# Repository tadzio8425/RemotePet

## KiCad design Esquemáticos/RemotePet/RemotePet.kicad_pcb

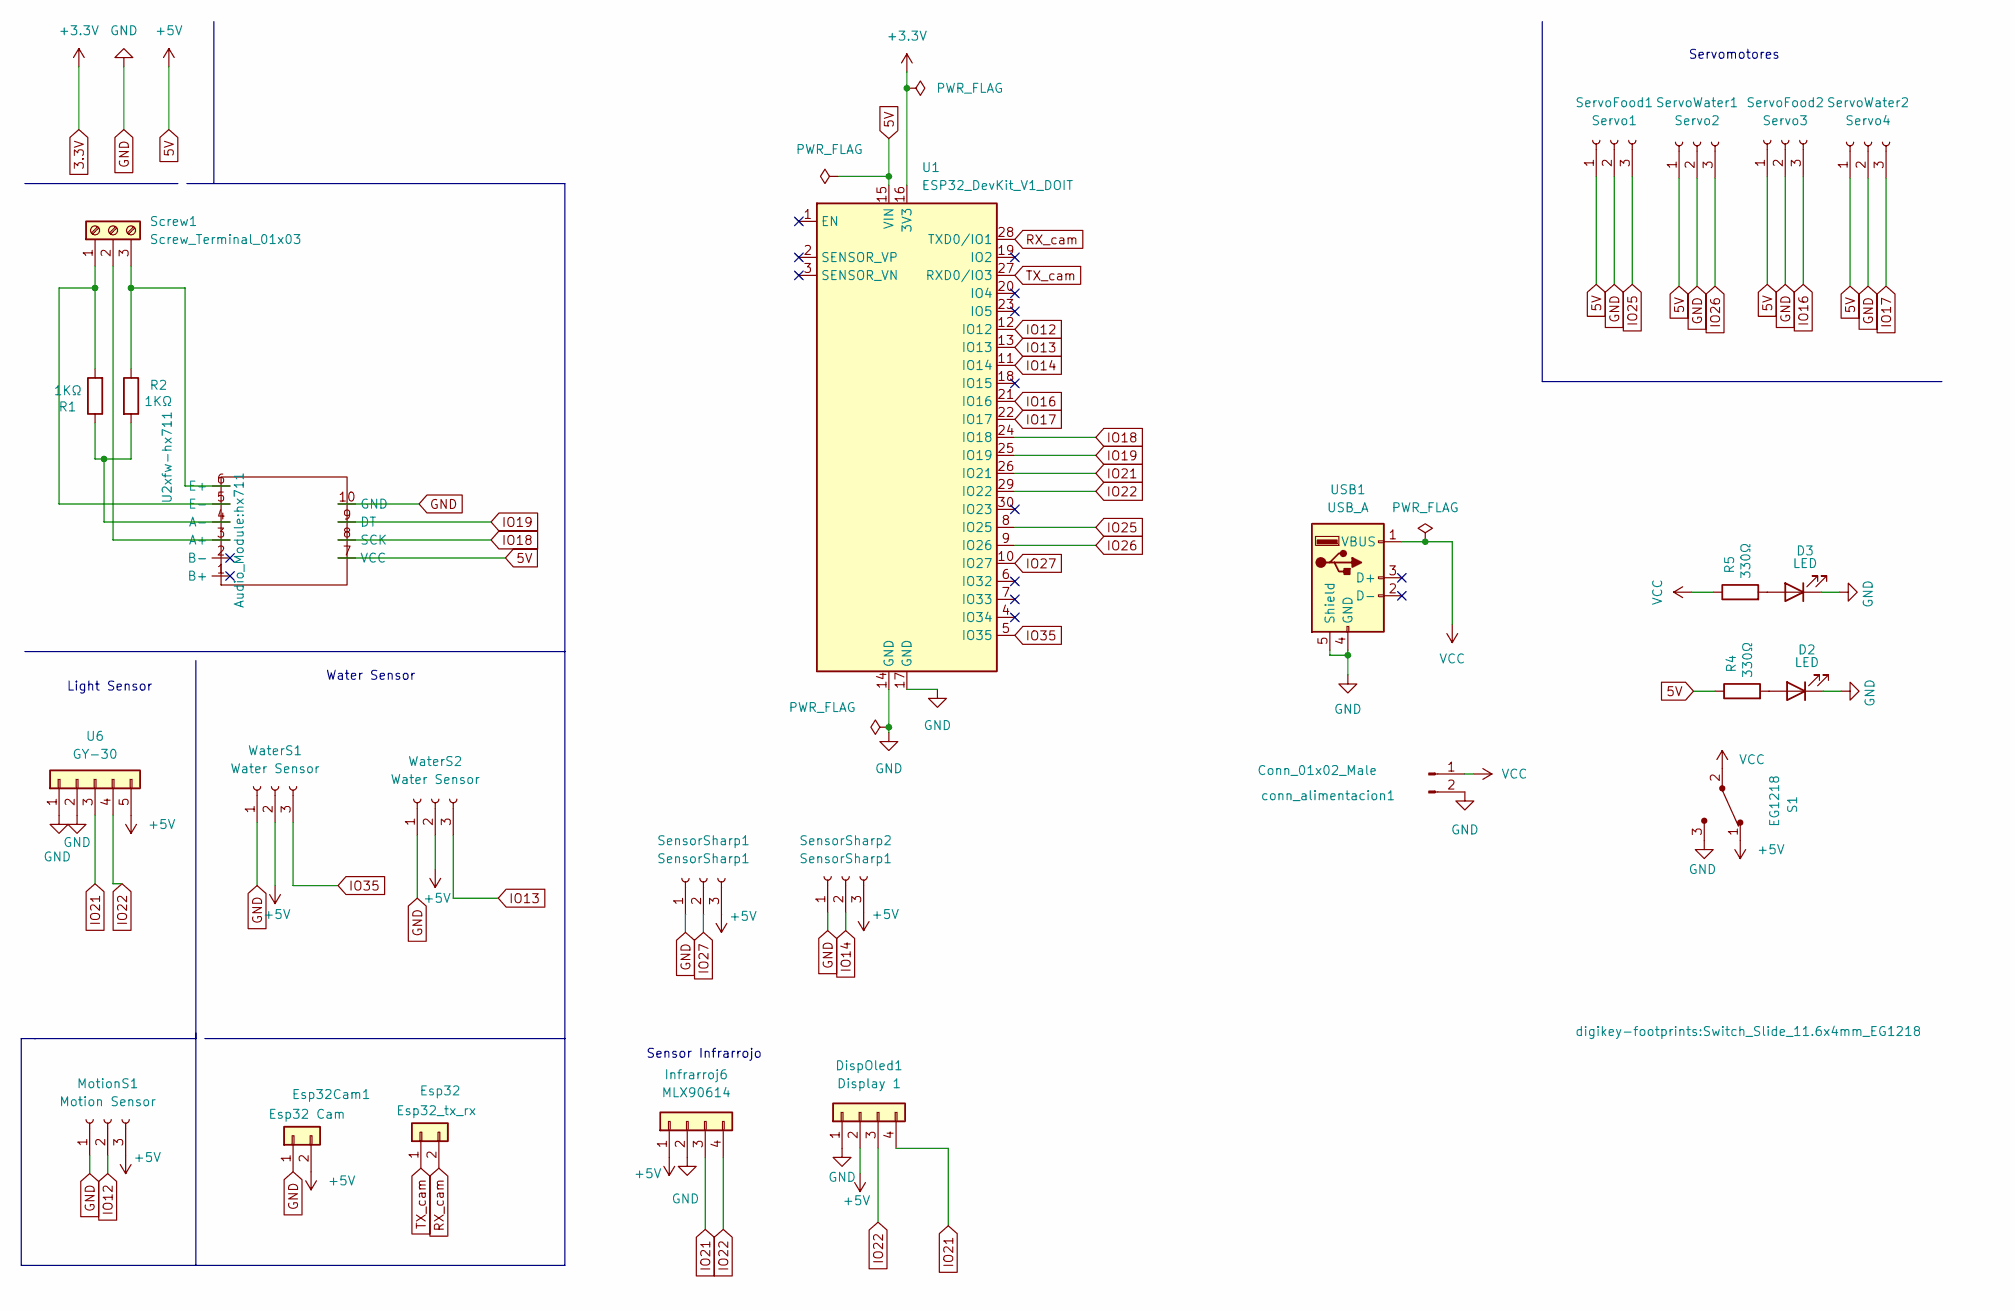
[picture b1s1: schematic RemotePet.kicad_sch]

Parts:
D2, D3: LED; LED_1210_3225Metric
DispOled1: Display 1; PinSocket_1x04_P2.54mm_Vertical
Esp32: Esp32_tx_rx; PinSocket_1x02_P2.54mm_Vertical
Esp32Cam1: Esp32 Cam; PinSocket_1x02_P2.54mm_Vertical
Infrarroj6: MLX90614; PinSocket_1x04_P2.54mm_Vertical
MotionS1: Motion Sensor; PinSocket_1x03_P2.54mm_Vertical
R1, R2: 1KΩ; R_0805_2012Metric
R4, R5: 330Ω; R_0805_2012Metric
S1: EG1218; Switch_Slide_11.6x4mm_EG1218; MPN EG1218; Digi-Key_PN EG1903-ND
Screw1: Screw_Terminal_01x03; TerminalBlock_bornier-3_P5.08mm
SensorSharp1, SensorSharp2: SensorSharp1; PinSocket_1x03_P2.54mm_Vertical
ServoFood1: Servo1; PinSocket_1x03_P2.54mm_Vertical
ServoFood2: Servo3; PinSocket_1x03_P2.54mm_Vertical
ServoWater1: Servo2; PinSocket_1x03_P2.54mm_Vertical
ServoWater2: Servo4; PinSocket_1x03_P2.54mm_Vertical
U1: ESP32_DevKit_V1_DOIT; esp32_devkit_v1_doit
U2: xfw-hx711; hx711
U6: GY-30; PinSocket_1x05_P2.54mm_Vertical
USB1: USB_A; USB_A_CONNFLY_DS1095-WNR0
WaterS1, WaterS2: Water Sensor; PinSocket_1x03_P2.54mm_Vertical
conn_alimentacion1: Conn_01x02_Male; PinSocket_1x02_P2.54mm_Vertical

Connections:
3.3V: U1.16 (3V3)
5V: DispOled1.2, Esp32Cam1.2, Infrarroj6.1, MotionS1.3, R4.1, S1.1, SensorSharp1.3, SensorSharp2.3, ServoFood1.1, ServoFood2.1, ServoWater1.1, ServoWater2.1, U1.15 (VIN), U2.7 (VCC), U6.5, WaterS1.2, WaterS2.2
GND: D2.1 (K), D3.1 (K), DispOled1.1, Esp32Cam1.1, Infrarroj6.2, MotionS1.1, S1.3, SensorSharp1.1, SensorSharp2.1, ServoFood1.2, ServoFood2.2, ServoWater1.2, ServoWater2.2, U1.14 (GND), U1.17 (GND), U2.10 (GND), U6.1, U6.2, USB1.4 (GND), USB1.5 (Shield), WaterS1.1, WaterS2.1, conn_alimentacion1.2
IO12: MotionS1.2, U1.12 (IO12)
IO13: U1.13 (IO13), WaterS2.3
IO14: SensorSharp2.2, U1.11 (IO14)
IO16: ServoFood2.3, U1.21 (IO16)
IO17: ServoWater2.3, U1.22 (IO17)
IO18: U1.24 (IO18), U2.8 (SCK)
IO19: U1.25 (IO19), U2.9 (DT)
IO21: DispOled1.4, Infrarroj6.3, U1.26 (IO21), U6.3
IO22: DispOled1.3, Infrarroj6.4, U1.29 (IO22), U6.4
IO25: ServoFood1.3, U1.8 (IO25)
IO26: ServoWater1.3, U1.9 (IO26)
IO27: SensorSharp1.2, U1.10 (IO27)
IO35: U1.5 (IO35), WaterS1.3
unnamed: D2.2 (A), R4.2
unnamed: R1.1, R2.2, U2.4 (A-)
unnamed: R1.2, Screw1.1, U2.5 (E-)
unnamed: R2.1, Screw1.3, U2.6 (E+)
unnamed: D3.2 (A), R5.2
unnamed: Screw1.2, U2.3 (A+)
RX_cam: Esp32.2, U1.28 (TXD0/IO1)
TX_cam: Esp32.1, U1.27 (RXD0/IO3)
VCC: R5.1, S1.2, USB1.1 (VBUS), conn_alimentacion1.1

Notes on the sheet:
Sensor Infrarrojo
Water Sensor
Light Sensor
Servomotores

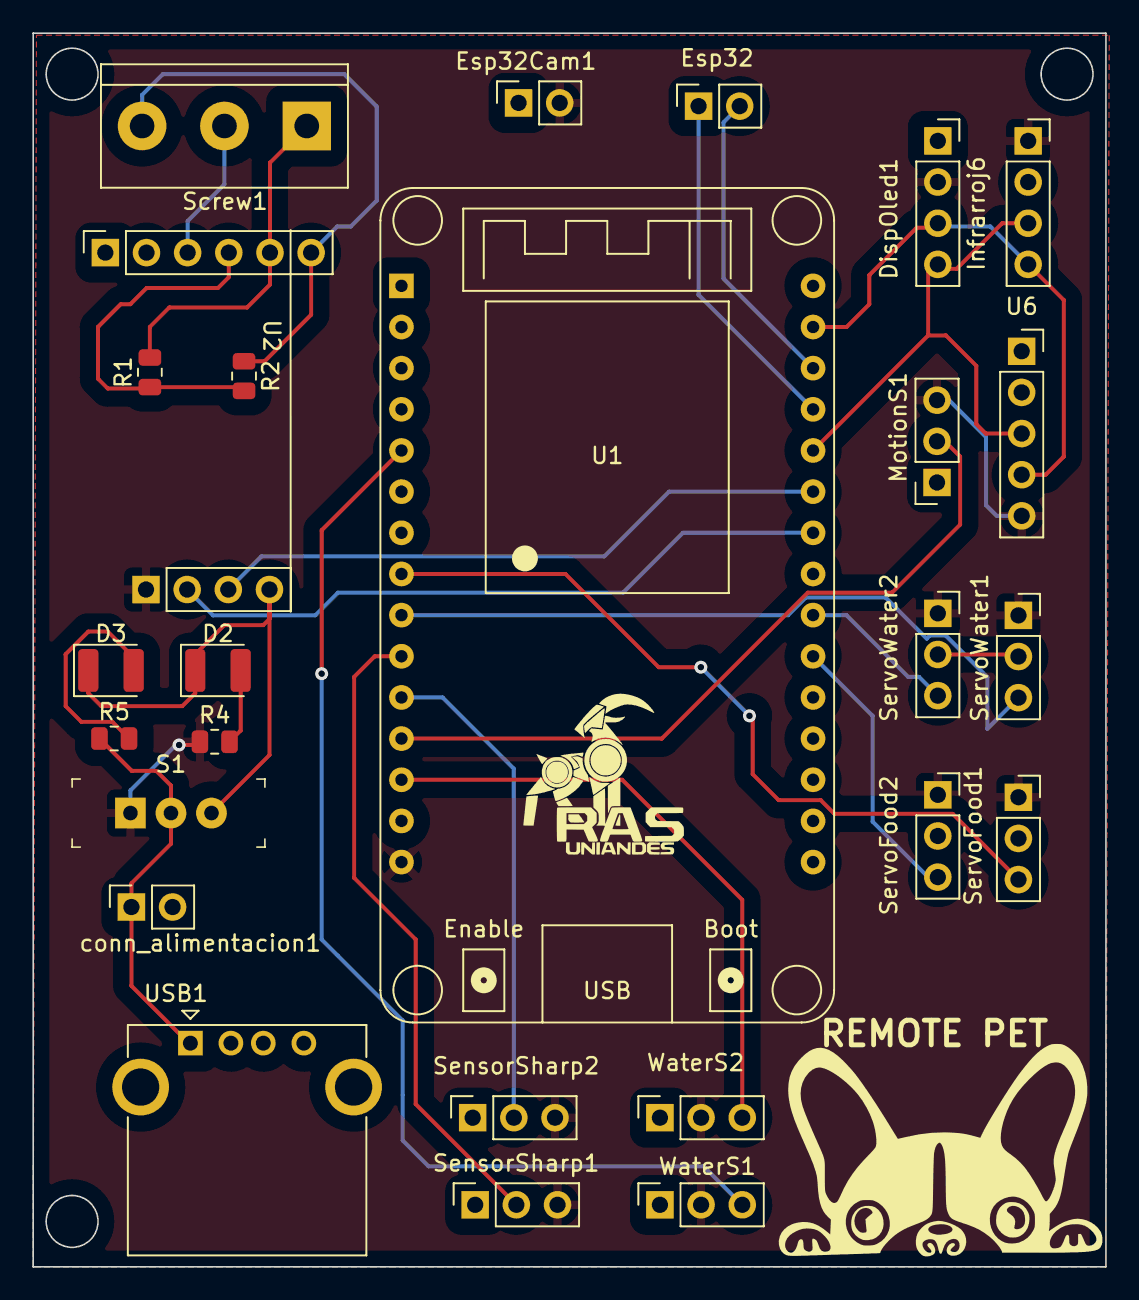
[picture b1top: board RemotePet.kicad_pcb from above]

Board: 2 copper layers, 66.2 x 76.1 mm, 27 parts (0 on the bottom side), 24 nets.

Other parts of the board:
REMOTE PET: LOGO; Perro

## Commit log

2022-04-09 Platformio source code
2022-04-09 Sensor de luz agregado
2022-04-09 Pines del sensor de luz agregados
2022-04-09 Water Sensor agregado
2022-04-09 Conexión a wifi
2022-04-09 Pruebas con los sockets
2022-04-09 Esquemático inicial
2022-04-09 Cambios adicionales
2022-04-09 Adelanto servos
2022-04-10 Update esquemático con servos
2022-04-10 Wireframes iniciales creados
2022-04-10 App GUI added
2022-04-10 Project moved
2022-04-10 Sensor status second activity added
2022-04-10 Avances conexión ESP32-App
2022-04-10 Sch-1
2022-04-10 Light sensor funcional y en la app!
2022-04-11 SCH_finish
2022-04-11 3 sensores terminados
2022-04-11 3 sensores app
2022-04-11 Alerta de conexión Wifi funcional!
2022-04-11 Logos e imágenes varios
2022-04-12 PCB-FINISH
2022-04-13 Drills PCB
2022-04-26 Remote-pet cam funcional!
2022-04-28 PCB 2.0
2022-05-16 Cambios que no tengo ni idea
2022-05-16 Camara agregada
2022-05-16 Cámara agregada 2
2022-05-16 Sensores dinámicos!
2022-05-18 Movement sensor added to code
2022-05-19 Water sensor intento de calibración
2022-05-20 Avances
2022-05-20 Prueba motores
2022-05-20 posición inicial motor setead
2022-05-20 Primera versipon funcional
2022-05-21 Sensor luz calibrado y room remp en app
2022-05-21 Pet temperature incluido
2022-05-21 Primer todo completado! - Movement sensor añadido
2022-05-21 envio de info timer - app a esp
2022-05-21 Hora recibida!
2022-05-21 Avance control servos con tiempo!
2022-05-21 pequeño ajuste
2022-05-22 Manual Feed funcionando!
2022-05-22 Water sensor re calibrado
2022-05-22 Versión pre final
2022-05-22 mini cambios
2022-05-22 Auto feed portions established!
2022-05-22 prociones del timer feed agregadas!
2022-05-22 Proyecto medianamente funcional!
